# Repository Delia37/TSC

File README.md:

# EBookReader

Am inceput implementarea proiectului pornind de la schema electrica data in enunt. Am luat pe rand componentele din biblioteca pusa la dispozitie, apoi le-am conctat si le-am pus label-urile. Am verificat cu ERC si am rezolvat erorile, majoritatea fiind de la pini suprapusi sau etichete puse prost. Am ramas cu o eroare pe care nu am putut sa o rezolv, deoarece Fusion nu i-a detectat locatia. Odata terminata schema electrica, am facut trecut la implementarea pcb-ului. Am decupat forma dupa dimensiunile cerute si am masurat laturile. Dificultatea cea mai mare de la acest pas a constat in identificarea pieselor. Dupa amplasarea lor, am rutat si am verificat cu regulile date in enunt. Aici a fost nevoie sa modific footprint-ul bobinei L1 pentru a nu mai avea erori. La final, am facut si planul de masa atat pe top, cat si pe bottom.

---

## Arhitectură Generală a Sistemului

ESP32-C6-WROOM-1-N8 acționează ca nod central, comunicând cu toate celelalte componente prin interfețe standard (I2C, SPI, GPIO). Alimentarea este asigurată de o baterie Li-Po controlată de un încărcător dedicat și monitorizată printr-un fuel gauge.

---

## Detalii Hardware

### ESP32-C6
- Procesor RISC-V cu conectivitate Wi-Fi 6 & BLE
- Comunicare: SPI, I2C, GPIO, UART
- Tensiune operare: 3.3V

### Management Energie
- MCP73831 – control încărcare baterie LiPo
- MAX17048 – monitorizare nivel baterie cu semnal alertă
- XC6220A331MR – stabilizare la 3.3V

### Senzori și RTC
- BME688 – monitorizare temperatură, umiditate, presiune, VOC (I2C)
- DS3231SN – ceas de timp real cu alarmă (I2C)

### Display și Stocare
- E-paper display – consum redus, ideal pentru afișaj static
- W25Q512JVEIQ – memorie NOR SPI externă, 64Mbit
- SD Card – opțional, conectat prin SPI partajat

### Protecție și Conectivitate
- Protecție ESD pe linii USB (USBLC6)
- Diode Schottky pentru protecție la supratensiune
- Port USB-C pentru alimentare și comunicație serială

### Interfețe Utilizator
- Buton RESET
- LED pentru starea încărcării

---

## Bill of Materials (CSV)

Fișierul complet BOM este disponibil aici: [Manufacturing/bom.csv](../Manufacturing/bom.csv)

---

## Alocare Pini ESP32-C6

| Componentă        | Pin ESP32 | Funcție        |
|------------------|-----------|----------------|
| BME688 – SDA     | IO8       | I2C SDA        |
| BME688 – SCL     | IO9       | I2C SCL        |
| DS3231SN – INT   | IO10      | Interrupt RTC  |
| W25Q512 – CS     | IO4       | SPI Flash CS   |
| E-Paper – CS     | IO3       | SPI Display CS |
| SPI – CLK        | IO5       | SPI Clock      |
| SPI – MOSI       | IO6       | SPI MOSI       |
| SPI – MISO       | IO7       | SPI MISO       |
| MAX17048 – ALERT | IO11      | Fuel Gauge INT |
| Buton RESET      | IO0       | Boot/Reset     |
| SD Card – CS     | IO2       | SPI CS SD Card |

---
## Imagini Asamblare și PCB

### Randare 3D

### PCB - Top Layer

### PCB - Bottom Layer

---

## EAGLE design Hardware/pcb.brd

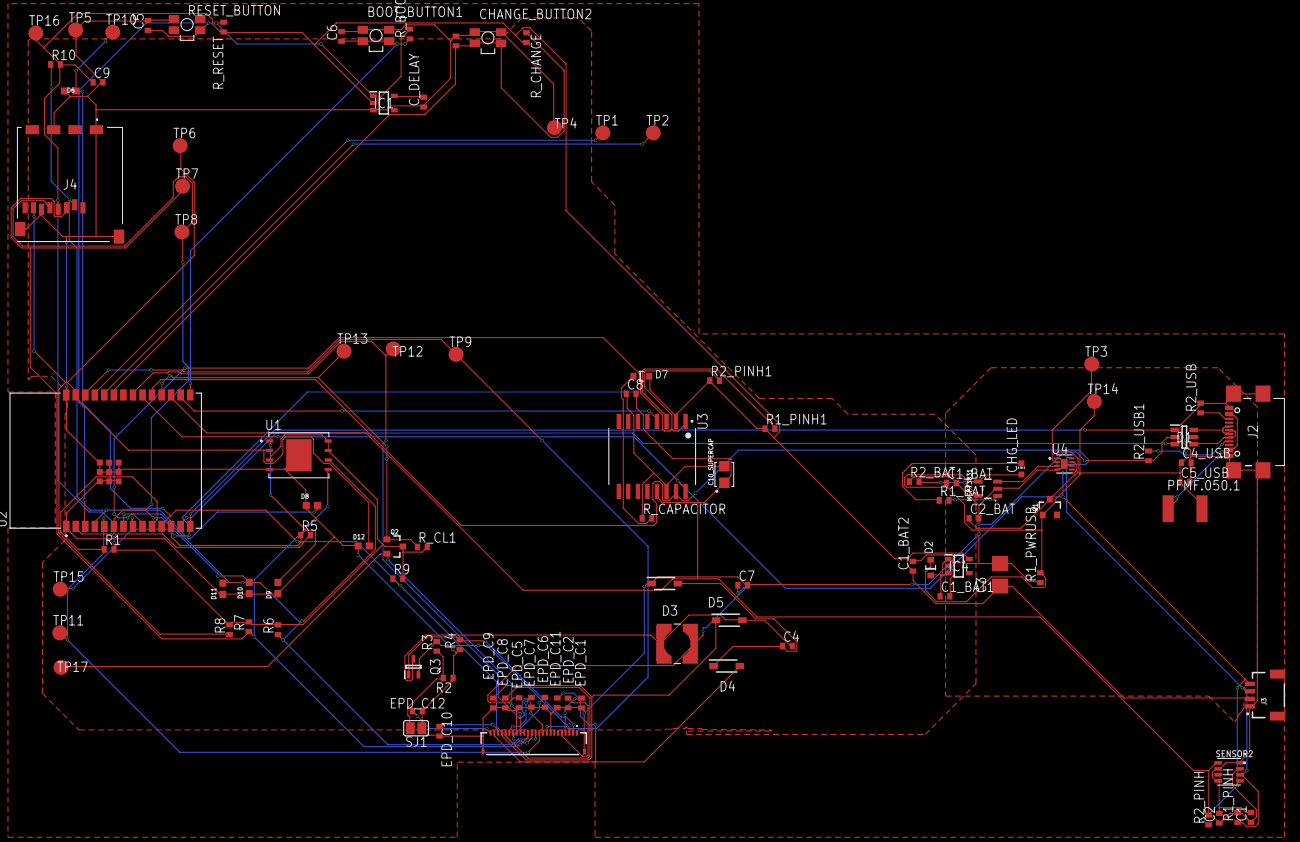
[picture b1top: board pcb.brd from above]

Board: 2 copper layers, 103 parts (0 on the bottom side), 55 nets.

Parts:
BOOT_BUTTON1: BUTTON_CUSYOMV1; MYBUTTON
C1, C2, C4_USB, C6, C8, C9, C10: 100nF; EAGLE-LTSPICE_C0402
C1_BAT, C1_BAT1, C1_BAT2, C2_BAT, C5_USB: 4.7uF; EAGLE-LTSPICE_C0402
C3: 100uF TANT; RCL_CT3528
C4: 4.7uF/25V; EAGLE-LTSPICE_C0402
C5: 1uF; EAGLE-LTSPICE_C0402
C7: 10uF; EAGLE-LTSPICE_C0402
C10_SUPERCAP: CPH3225A; CAPCP3225X100N
CHANGE_BUTTON2: BUTTON_CUSYOMV1; MYBUTTON
CHG_LED: ADAFRUIT_CHIP-LED0603
C_DELAY: 100nF; EAGLE-LTSPICE_C0402
D1: USBLC6-2SC6Y; SOT95P280X145-6N
D2, D7: ESP32_WROVER_AVX---SD0805S020S1R0_AVX_SD0805S020S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; ESP32_WROVER_AVX---SD0805S020S1R0_AVX_SD0805S020S1R0_0
D3, D4, D5: MBR0530; SOD3716X135N
D6, D8, D9, D10, D11, D12: PGB1010603MR; DIOC1608X36N
EPD_C1, EPD_C2, EPD_C6, EPD_C7, EPD_C8, EPD_C9, EPD_C10, EPD_C11, EPD_C12: 1uF/50V; EAGLE-LTSPICE_C0402
EPD_C5: 0.1uF/50V; EAGLE-LTSPICE_C0402
FH34SRJ-24S-0.5SH_99_: FH34SRJ-24S-0.5SH_99_; FH34SRJ24S05SH99
IC1: BD5229G-TR; SOT95P280X125-5N
IC4: XC6220A331MR-G; SOT95P280X120-5N
J2: SAMACSYS_PARTS_USB4110-GF-A; SAMACSYS_PARTS_USB4110GFA
J3: QWIIC_RIGHT_ANGLE; JST04_1MM_RA
J4: 112A-TAAR-R03_ATTEND; 112ATAARR03ATTEND
L1: 68uH; IND_4828-WE-TPC_WRE
MCP73831: ESP32_WROVER_SPARKFUN-IC-POWER_MCP73831; ESP32_WROVER_SPARKFUN-IC-POWER_SOT23-5
PFMF.050.1: ESP32C6_VARISTORCN1812; ESP32C6_VARISTOR_CT/CN1812
Q1, Q2: 20V/4.2A/52mΩ/1.4W; ESP32_WROVER_SPARKFUN-DISCRETESEMI_SOT23-3
Q3: SI1308EDL-T1-GE3; SOT65P210X110-3N
R1, R1_PINH, R1_PINH1, R2_PINH, R2_PINH1, R4: 10k; ESP32_WROVER_EAGLE-LTSPICE_R0402
R1_BAT: 200; ESP32_WROVER_EAGLE-LTSPICE_R0402
R1_PWRUSB: 100k; ESP32_WROVER_EAGLE-LTSPICE_R0402
R2: 2.2; ESP32_WROVER_EAGLE-LTSPICE_R0402
R2_BAT: 2K; ESP32_WROVER_EAGLE-LTSPICE_R0402
R2_USB, R2_USB1: 5k1; ESP32_WROVER_EAGLE-LTSPICE_R0402
R3: 0.47; ESP32_WROVER_EAGLE-LTSPICE_R0402
R5, R6, R7, R8, R9, R10: 10K; ESP32_WROVER_EAGLE-LTSPICE_R0402
RESET_BUTTON: BUTTON_CUSYOMV1; MYBUTTON
R_BOOT: 10K; ESP32_WROVER_EAGLE-LTSPICE_R0402
R_CAPACITOR: 15; ESP32_WROVER_EAGLE-LTSPICE_R0402
R_CHANGE: 10K; ESP32_WROVER_EAGLE-LTSPICE_R0402
R_CL1: 10k; ESP32_WROVER_EAGLE-LTSPICE_R0402
R_RESET: 10K; ESP32_WROVER_EAGLE-LTSPICE_R0402
SENSOR2: ESP32_WROVER_BME680_BME680; ESP32_WROVER_BME680_PSON80P300X300X100-8N
SJ1: SJ
TP1, TP2, TP3, TP4, TP5, TP6, TP7, TP8, TP9, TP10, TP11, TP12, TP13, TP14, TP15, TP16, TP17: TPTP20R; TP20R
U1: W25Q512JVEIQ; SON127P600X800X80-9N
U2: ESP32-C6-WROOM-1-N8; XCVR_ESP32-C6-WROOM-1-N8
U3: DS3231SN#; SOIC127P1032X265-16N
U4: MAX17048G+T10; SON50P200X200X80-9N

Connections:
3V3: C1_BAT2.1, C3.+, C9.1, D7.2, IC1.2, IC4.5, J3.2, J4.P4, Q2.3, R1.2, R1_PINH1.1, R2_PINH1.1, R5.2, R6.2, R7.2, R8.2, R9.2, R10.2, R_BOOT.2, R_CHANGE.2, R_CL1.2, R_RESET.2, TP16.TP, U1.3, U1.7, U1.8, U2.2, U3.2
32KHZ: R2_PINH1.2, U2.9, U3.1
DN: D1.4, J2.A7, J2.B7
DP: D1.6, J2.A6, J2.B6
EPD_3V3: C7.1, EPD_C5.2, FH34SRJ-24S-0.5SH_99_.15, FH34SRJ-24S-0.5SH_99_.16, L1.2, Q2.2, TP17.TP
EPD_3V3_C: Q2.1, R_CL1.1, TP13.TP, U2.18
EPD_BUSY: FH34SRJ-24S-0.5SH_99_.9, TP9.TP, U2.26
EPD_CS: D6.2, FH34SRJ-24S-0.5SH_99_.12, R9.1, TP10.TP, U2.11
EPD_DC: FH34SRJ-24S-0.5SH_99_.11, TP11.TP, U2.5
EPD_RST: FH34SRJ-24S-0.5SH_99_.10, TP12.TP, U2.21
FLASH_CS: D9.2, R5.1, U1.1, U2.12
GDR: FH34SRJ-24S-0.5SH_99_.2, Q3.1, R4.2
GND: BOOT_BUTTON1.1, BOOT_BUTTON1.2, C1.2, C1_BAT.2, C1_BAT1.2, C1_BAT2.2, C2.2, C2_BAT.2, C3.-, C4_USB.2, C5.2, C5_USB.2, C6.2, C7.2, C8.2, C9.2, C10.2, C10_SUPERCAP.1, CHANGE_BUTTON2.1, CHANGE_BUTTON2.2, C_DELAY.1, D1.2, D3.1, D6.1, D8.1, D9.1, D10.1, D11.1, D12.1, EPD_C1.1, EPD_C2.1, EPD_C5.1, EPD_C6.1, EPD_C7.1, EPD_C8.1, EPD_C9.1, EPD_C10.1, EPD_C11.1, EPD_C12.1, FH34SRJ-24S-0.5SH_99_.8, FH34SRJ-24S-0.5SH_99_.17, FH34SRJ-24S-0.5SH_99_.MP1, FH34SRJ-24S-0.5SH_99_.MP2, IC1.3, IC4.2, J2.A1, J2.A12, J2.B1, J2.B12, J2.MP1, J2.MP2, J2.MP3, J2.MP4, J3.1, J4.G1, J4.G2, J4.G3, J4.G4, J4.P6, MCP73831.2, R1_PWRUSB.1, R2.1, R2_BAT.1, R2_USB.2, R2_USB1.1, R4.1, RESET_BUTTON.2, SENSOR2.1, SENSOR2.5, SENSOR2.7, SJ1.1, TP4.TP, TP5.TP, U1.4, U1.9, U2.1, U2.28, U2.29_1, U2.29_2, U2.29_3, U2.29_4, U2.29_5, U2.29_6, U2.29_7, U2.29_8, U2.29_9, U3.13, U4.1, U4.4, U4.6, U4.9
GPIO8: R1.1, U2.10
I2C_PW: C1.1, C2.1, R1_PINH.2, R2_PINH.2, SENSOR2.2, SENSOR2.6, SENSOR2.8, U2.17
INT_RTC: R1_PINH1.2, TP15.TP, U2.8, U3.3
IO/BOOT: BOOT_BUTTON1.3, BOOT_BUTTON1.4, C6.1, R_BOOT.1, U2.15
IO/CHANGE: C10.1, CHANGE_BUTTON2.3, CHANGE_BUTTON2.4, R_CHANGE.1, U2.23
MISO: D12.2, J4.P7, R8.1, TP6.TP, U1.2, U2.27
MOSI: D11.2, FH34SRJ-24S-0.5SH_99_.14, J4.P3, R7.1, TP7.TP, U1.5, U2.7
unnamed: J2.A5, R2_USB1.2
unnamed: J2.B5, R2_USB.1
unnamed: D7.1, R_CAPACITOR.2
unnamed: MCP73831.1, R1_BAT.2
unnamed: C4.1, D3.2, D4.1
unnamed: CHG_LED.C, R1_BAT.1
unnamed: MCP73831.5, R2_BAT.2
unnamed: EPD_C12.2, FH34SRJ-24S-0.5SH_99_.24
unnamed: EPD_C8.2, FH34SRJ-24S-0.5SH_99_.20
unnamed: EPD_C10.2, FH34SRJ-24S-0.5SH_99_.22
unnamed: EPD_C7.2, FH34SRJ-24S-0.5SH_99_.19
unnamed: EPD_C6.2, FH34SRJ-24S-0.5SH_99_.18
unnamed: EPD_C2.2, FH34SRJ-24S-0.5SH_99_.5
unnamed: EPD_C1.2, FH34SRJ-24S-0.5SH_99_.4
unnamed: C_DELAY.2, IC1.5
unnamed: C1_BAT1.1, D2.1, IC4.1, IC4.3
PREVGH: D5.1, EPD_C9.2, FH34SRJ-24S-0.5SH_99_.21
PREVGL: D4.2, EPD_C11.2, FH34SRJ-24S-0.5SH_99_.23
RESE: FH34SRJ-24S-0.5SH_99_.3, Q3.2, R3.2
RESE': R2.2, R3.1, SJ1.2
RESET: C5.1, IC1.1, RESET_BUTTON.4, R_RESET.1, U2.3
RTC_RST: U2.16, U3.4
RX: TP2.TP, U2.24
SCK: D10.2, FH34SRJ-24S-0.5SH_99_.13, J4.P5, R6.1, TP8.TP, U1.6, U2.6
SCL: J3.4, R2_PINH.1, SENSOR2.4, U2.20, U3.16, U4.7
SDA: J3.3, R1_PINH.1, SENSOR2.3, U2.19, U3.15, U4.8
SRC: C4.2, D5.2, L1.1, Q3.3
SS_SD: D8.2, J4.P2, R10.1, U2.4
TX: TP1.TP, U2.25
USB_D+: D1.1, U2.14
USB_D-: D1.3, U2.13
VBAT: C2_BAT.1, MCP73831.3, Q1.3, TP3.TP, U4.2, U4.3
VBUS: C1_BAT.1, C4_USB.1, C5_USB.1, CHG_LED.A, D1.5, D2.2, MCP73831.4, PFMF.050.1.2, Q1.1, R1_PWRUSB.2, TP14.TP
VRTC: C8.1, C10_SUPERCAP.2, R_CAPACITOR.1, U3.14
VUSB: J2.A4, J2.A9, J2.B4, J2.B9, PFMF.050.1.1

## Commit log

2025-04-06 Resolved merge conflicts
2025-04-15 Create LICENSE

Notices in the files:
parts and their libraries:
COPYRIGHT: Copyright (C) 2024 Ultra Librarian. All rights reserved.
